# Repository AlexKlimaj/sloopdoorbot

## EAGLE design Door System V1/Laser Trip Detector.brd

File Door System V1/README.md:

Directional-Digital-Turnstile
=============================

This project aims to create a directional digital turnstile to serve as a doorbell and to gather statistics about the number of people in a facility.

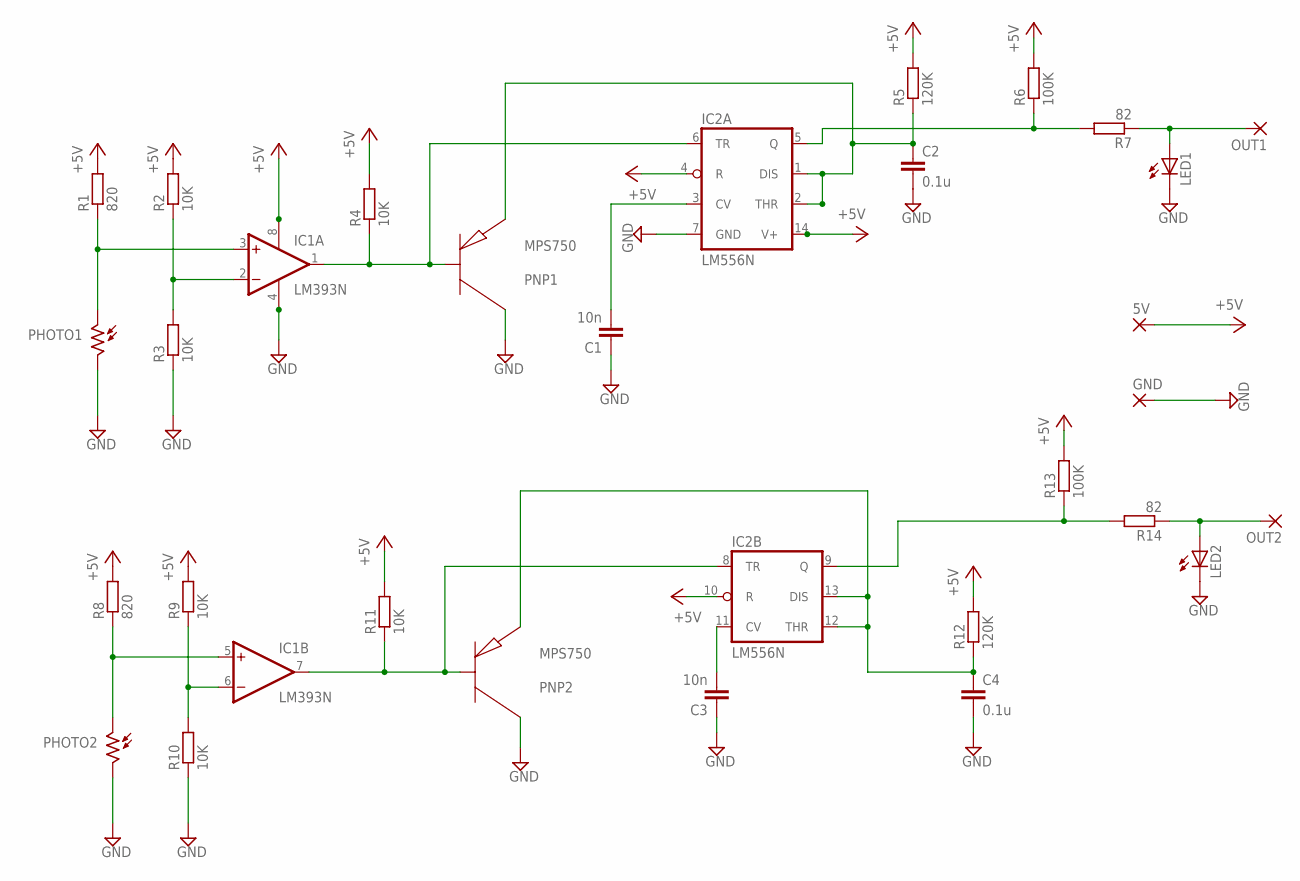
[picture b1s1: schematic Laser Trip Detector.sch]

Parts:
5V: 3,17/1,3
C1, C3: 10n; C5B3
C2, C4: 0.1u; C5B3
GND: 3,17/1,3
IC1: LM393N; DIL08
IC2: LM556N; DIL14
LED1, LED2: LED5MM
OUT1, OUT2: 3,17/1,3
PHOTO1, PHOTO2: M9960_11A; M9960
PNP1, PNP2: MPS750; TO92
R1, R8: 820; 0207/10
R2, R3, R4, R9, R10, R11: 10K; 0207/10
R5, R12: 120K; 0207/10
R6, R13: 100K; 0207/10
R7, R14: 82; 0207/10

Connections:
+5V: 5V.1, IC1.8 (V+), IC2.4 (R), IC2.10 (R), IC2.14 (V+), R1.2, R2.2, R4.2, R5.2, R6.2, R8.2, R9.2, R11.2, R12.2, R13.2
GND: C1.1, C2.2, C3.1, C4.2, GND.1, IC1.4 (V-), IC2.7 (GND), LED1.K (C), LED2.K (C), PHOTO1.2, PHOTO2.2, PNP1.1 (C), PNP2.1 (C), R3.1, R10.1
unnamed: IC1.2 (-IN), R2.1, R3.2
unnamed: IC1.3 (+IN), PHOTO1.1, R1.1
unnamed: IC1.1 (OUT), IC2.6 (TR), PNP1.2 (B), R4.1
unnamed: C1.2, IC2.3 (CV)
unnamed: C2.1, IC2.1 (DIS), IC2.2 (THR), PNP1.3 (E), R5.1
unnamed: IC2.5 (Q), R6.1, R7.2
unnamed: LED1.A, OUT1.1, R7.1
unnamed: IC1.6 (-IN), R9.1, R10.2
unnamed: IC1.5 (+IN), PHOTO2.1, R8.1
unnamed: IC1.7 (OUT), IC2.8 (TR), PNP2.2 (B), R11.1
unnamed: C3.2, IC2.11 (CV)
unnamed: C4.1, IC2.12 (THR), IC2.13 (DIS), PNP2.3 (E), R12.1
unnamed: IC2.9 (Q), R13.1, R14.2
unnamed: LED2.A, OUT2.1, R14.1

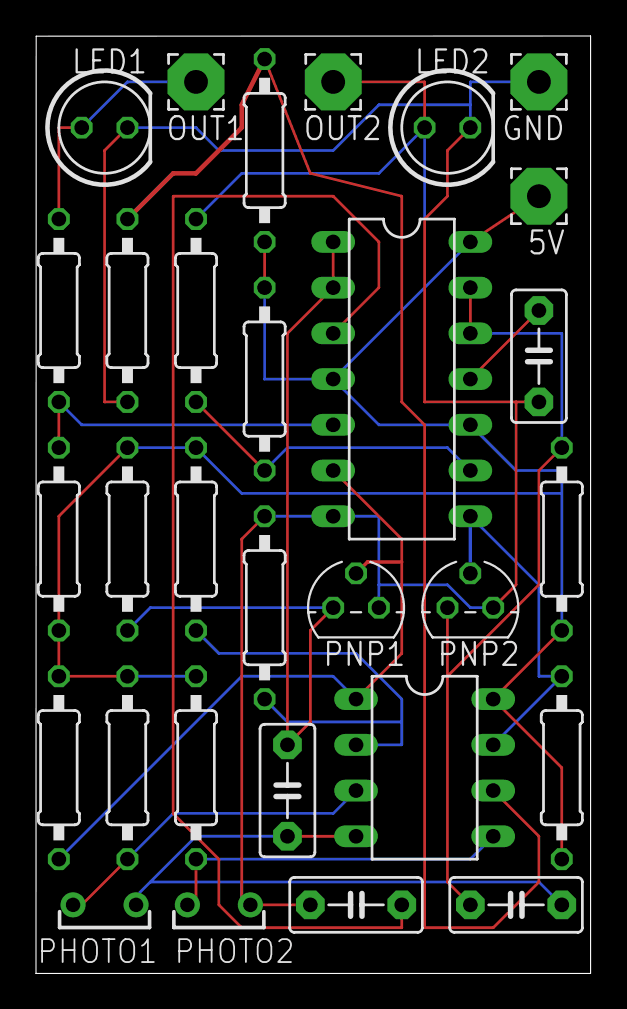
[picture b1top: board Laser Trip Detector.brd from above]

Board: 2 copper layers, 30.8 x 52.1 mm, 30 parts (0 on the bottom side), 16 nets.

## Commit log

2015-10-02 Initial Add
2015-10-02 Report
